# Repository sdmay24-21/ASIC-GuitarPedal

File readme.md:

# Digital ASIC Fabrication
Guitar Pedal IC

Top Level Diagram
## Members
Jonathan Hess\
Haris Khan\
Samuel Heikens\
Yu Wei Tan

## References
Audio samples:

https://shop.karoryfer.com/pages/free-samples

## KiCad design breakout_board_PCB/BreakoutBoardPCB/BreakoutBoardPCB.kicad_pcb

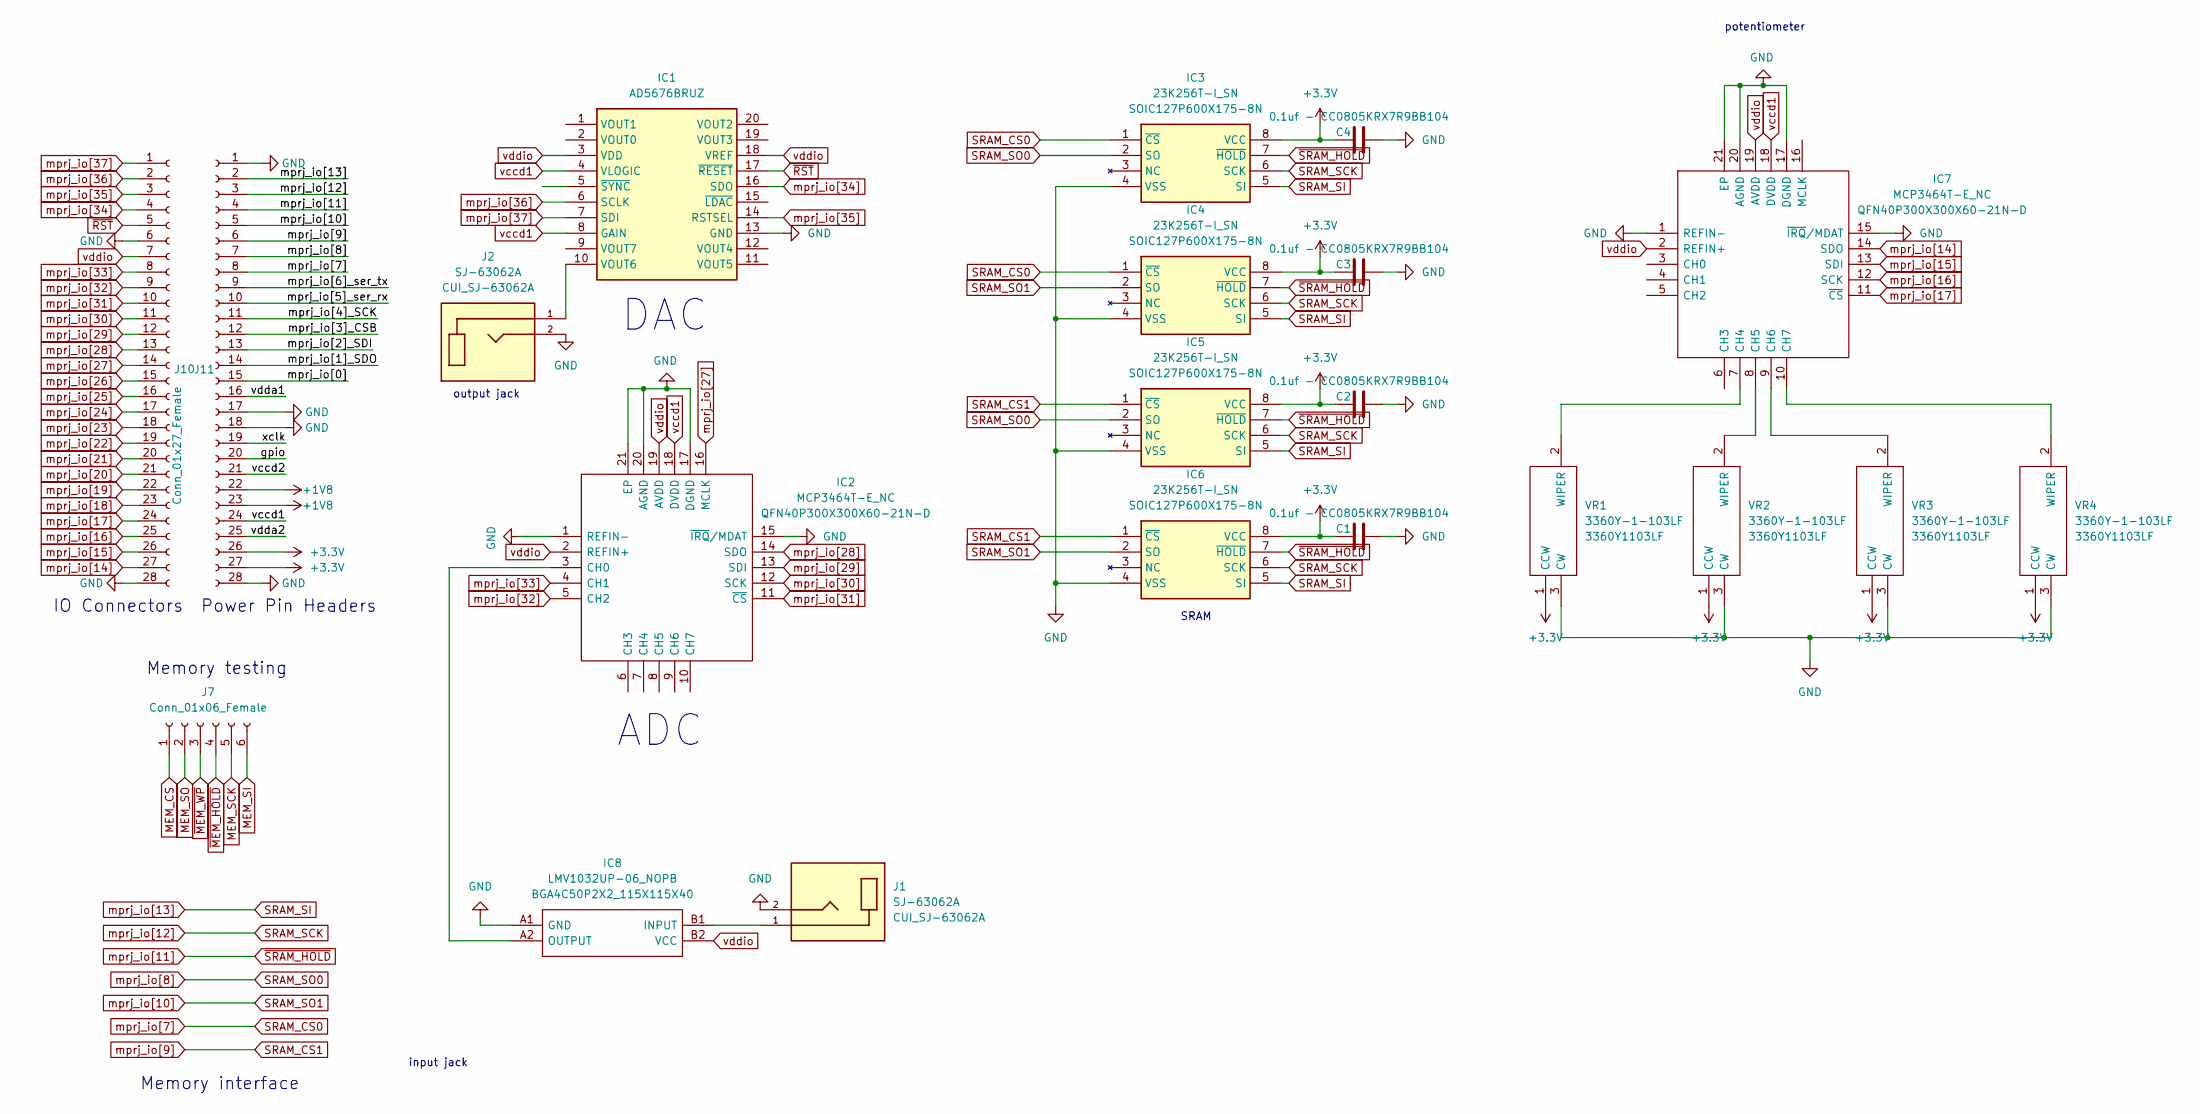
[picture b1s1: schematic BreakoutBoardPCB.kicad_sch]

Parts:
C1, C2, C3, C4: 0.1uf - CC0805KRX7R9BB104; C_0805_2012Metric
IC1: AD5676BRUZ; SOP65P640X120-20N; Mouser Part Number 584-AD5676BRUZ
IC2, IC7: MCP3464T-E_NC; QFN40P300X300X60-21N-D; Mouser Part Number 579-MCP3464T-E/NC
IC3, IC4, IC5, IC6: 23K256T-I_SN; SOIC127P600X175-8N; Mouser Part Number 579-23K256T-I/SN
IC8: LMV1032UP-06_NOPB; BGA4C50P2X2_115X115X40; Mouser Part Number 926-LMV1032UP06NOPB
J1, J2: SJ-63062A; CUI_SJ-63062A
J7: Conn_01x06_Female; PinHeader_1x06_P2.54mm_Vertical
J10: Conn_01x27_Female; PinHeader_1x27_P2.54mm_Vertical
J11: Conn_01x28_Pin; PinHeader_1x28_P2.54mm_Vertical
VR1, VR2, VR3, VR4: 3360Y-1-103LF; 3360Y1103LF; Mouser Part Number 652-3360Y-1-103LF

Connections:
+1V8: J11.22, J11.23
+3.3V: C1.1, C2.1, C3.1, C4.1, IC3.8 (VCC), IC4.8 (VCC), IC5.8 (VCC), IC6.8 (VCC), J11.26, J11.27, VR1.1 (CCW), VR2.1 (CCW), VR3.1 (CCW), VR4.1 (CCW)
/gpio: J11.20
/mprj_io[0]: J11.15
/mprj_io[1]_SDO: J11.14
/mprj_io[2]_SDI: J11.13
/mprj_io[3]_CSB: J11.12
/mprj_io[4]_SCK: J11.11
/mprj_io[5]_ser_rx: J11.10
/mprj_io[6]_ser_tx: J11.9
/vccd2: J11.21
/vdda1: J11.16
/vdda2: J11.25
/xclk: J11.19
GND: C1.2, C2.2, C3.2, C4.2, IC1.13 (GND), IC2.1 (REFIN-), IC2.15 (~IRQ/MDAT), IC2.17 (DGND), IC2.20 (AGND), IC2.21 (EP), IC3.4 (VSS), IC4.4 (VSS), IC5.4 (VSS), IC6.4 (VSS), IC7.1 (REFIN-), IC7.15 (~IRQ/MDAT), IC7.17 (DGND), IC7.20 (AGND), IC7.21 (EP), IC8.A1 (GND), J1.2, J2.2, J10.6, J10.28, J11.1, J11.17, J11.18, J11.28, VR1.3 (CW), VR2.3 (CW), VR3.3 (CW), VR4.3 (CW); also elsewhere on the board
MEM_CS: J7.1
MEM_SCK: J7.5
MEM_SI: J7.6
MEM_SO: J7.2
unnamed: IC1.10 (VOUT6), J2.1
unnamed: IC2.3 (CH0), IC8.A2 (OUTPUT)
unnamed: IC7.7 (CH4), VR1.2 (WIPER)
unnamed: IC7.8 (CH5), VR2.2 (WIPER)
unnamed: IC7.9 (CH6), VR3.2 (WIPER)
unnamed: IC7.10 (CH7), VR4.2 (WIPER)
unnamed: IC8.B1 (INPUT), J1.1
SRAM_CS0: IC3.1 (~CS), IC4.1 (~CS), J11.8
SRAM_CS1: IC5.1 (~CS), IC6.1 (~CS), J11.6
SRAM_SCK: IC3.6 (SCK), IC4.6 (SCK), IC5.6 (SCK), IC6.6 (SCK), J11.3
SRAM_SI: IC3.5 (SI), IC4.5 (SI), IC5.5 (SI), IC6.5 (SI), J11.2
SRAM_SO0: IC3.2 (SO), IC5.2 (SO), J11.7
SRAM_SO1: IC4.2 (SO), IC6.2 (SO), J11.5
mprj_io[11]: IC3.7 (~HOLD), IC4.7 (~HOLD), IC5.7 (~HOLD), IC6.7 (~HOLD), J11.4
mprj_io[14]: IC7.14 (SDO), J10.27
mprj_io[15]: IC7.13 (SDI), J10.26
mprj_io[16]: IC7.12 (SCK), J10.25
mprj_io[17]: IC7.11 (~CS), J10.24
mprj_io[18]: J10.23
mprj_io[19]: J10.22
mprj_io[20]: J10.21
mprj_io[21]: J10.20
mprj_io[22]: J10.19
mprj_io[23]: J10.18
mprj_io[24]: J10.17
mprj_io[25]: J10.16
mprj_io[26]: J10.15
mprj_io[27]: IC2.16 (MCLK), J10.14
mprj_io[28]: IC2.14 (SDO), J10.13
mprj_io[29]: IC2.13 (SDI), J10.12
mprj_io[30]: IC2.12 (SCK), J10.11
mprj_io[31]: IC2.11 (~CS), J10.10
mprj_io[32]: IC2.5 (CH2), J10.9
mprj_io[33]: IC2.4 (CH1), J10.8
mprj_io[34]: IC1.16 (SDO), J10.4
mprj_io[35]: IC1.14 (RSTSEL), J10.3
mprj_io[36]: IC1.6 (SCLK), J10.2
mprj_io[37]: IC1.7 (SDI), J10.1
vccd1: IC1.4 (VLOGIC), IC1.8 (GAIN), IC2.18 (DVDD), IC7.18 (DVDD), J11.24
vddio: IC1.3 (VDD), IC1.18 (VREF), IC2.2 (REFIN+), IC2.19 (AVDD), IC7.2 (REFIN+), IC7.19 (AVDD), IC8.B2 (VCC), J10.7
~MEM_HOLD: J7.4
~MEM_WP: J7.3
~RST: IC1.17 (~RESET), J10.5

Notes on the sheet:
SRAM
potentiometer
Power Pin Headers
ADC
Memory interface
Memory testing
output jack
DAC
IO Connectors
input jack

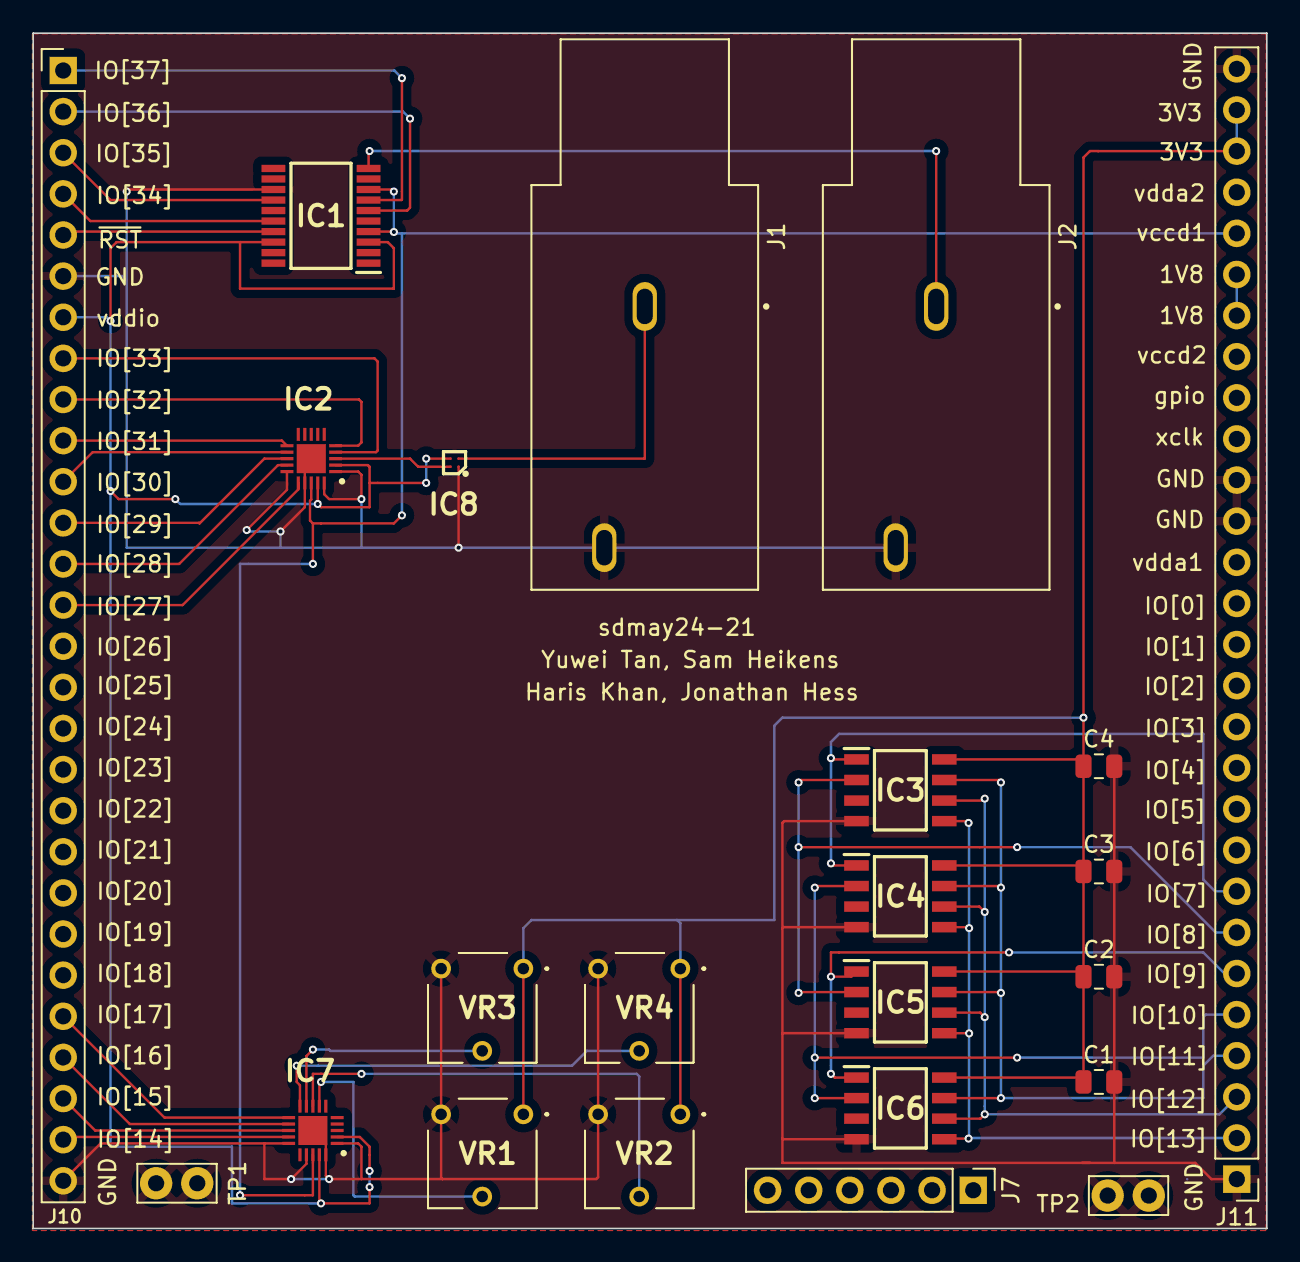
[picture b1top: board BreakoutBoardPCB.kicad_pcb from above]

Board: 2 copper layers, 76.2 x 73.8 mm, 23 parts (0 on the bottom side), 35 nets.

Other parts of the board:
TP1, TP2: TestPoint; TestPoint_Bridge_Pitch2.54mm_Drill1.0mm

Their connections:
GND: TP1.1, TP2.1; also elsewhere on the board

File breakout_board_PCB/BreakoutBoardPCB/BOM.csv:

"Reference","Value","Datasheet","Footprint","Qty","DNP"
"C1,C2,C3,C4","0.1uf - CC0805KRX7R9BB104","~","Capacitor_SMD:C_0805_2012Metric","4",""
"IC1","AD5676BRUZ","https://www.analog.com/AD5676/datasheet","SeniorDesign:SOP65P640X120-20N","1",""
"IC2,IC7","MCP3464T-E_NC","http://www.microchip.com/mymicrochip/filehandler.aspx?ddocna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","QFN40P300X300X60-21N-D","2",""
"IC3,IC4,IC5,IC6","23K256T-I_SN","http://www.microchip.com/mymicrochip/filehandler.aspx?ddocna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","SOIC127P600X175-8N","4",""
"IC8","LMV1032UP-06_NOPB","http://www.ti.com/lit/gpn/lmv1032","BGA4C50P2X2_115X115X40","1",""
"J1,J2","SJ-63062A","","CUI_SJ-63062A","2",""
"J7","Conn_01x06_Female","~","Connector_PinHeader_2.54mm:PinHeader_1x06_P2.54mm_Vertical","1",""
"J10","Conn_01x27_Female","~","Connector_PinHeader_2.54mm:PinHeader_1x27_P2.54mm_Vertical","1",""
"J11","Conn_01x28_Pin","~","Connector_PinHeader_2.54mm:PinHeader_1x28_P2.54mm_Vertical","1",""
"VR1,VR2,VR3,VR4","3360Y-1-103LF","http://www.bourns.com/docs/Product-Datasheets/3360.pdf","3360Y1103LF","4",""

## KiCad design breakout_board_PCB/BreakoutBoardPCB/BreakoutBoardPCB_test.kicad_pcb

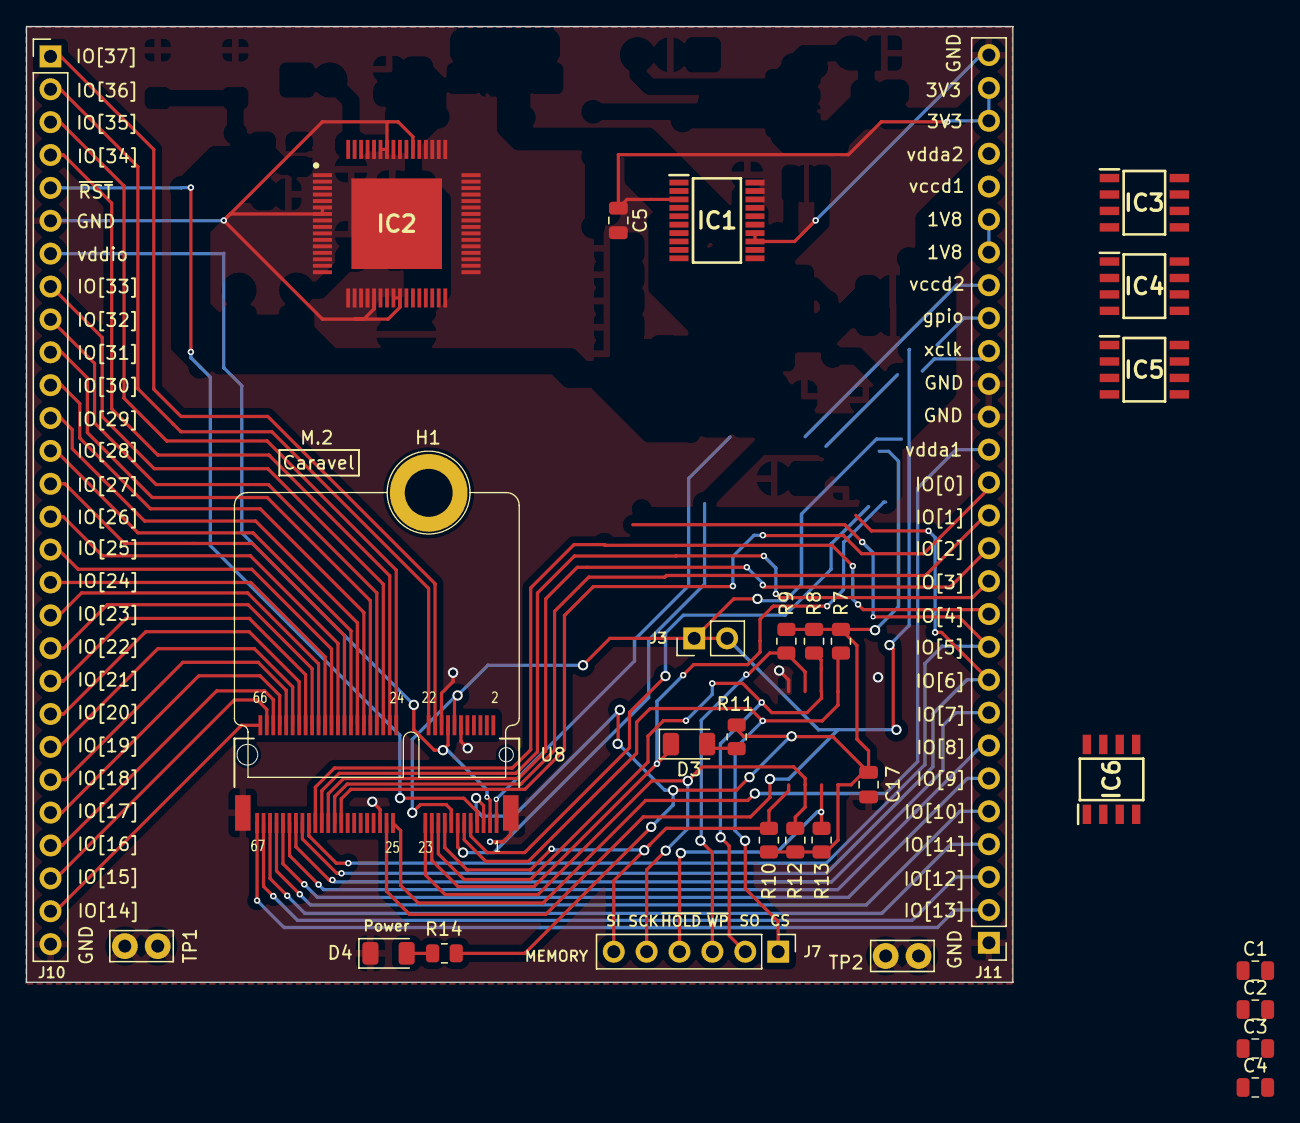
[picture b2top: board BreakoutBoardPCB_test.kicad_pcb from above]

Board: 2 copper layers, 76.2 x 73.8 mm, 30 parts (0 on the bottom side), 56 nets.

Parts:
C1, C2, C3, C4, C5, C17: 0.1uf - CC0805KRX7R9BB104; C_0805_2012Metric
D3, D4: LED - 17-215SURC/S530-A2/TR8; LED_1206_3216Metric
H1: MICROMOD-Standoff; MicroMod-Standoff
IC1: AD5676BRUZ; SOP65P640X120-20N
IC2: ADS1178IPAPT; QFP50P1200X1200X120-65N
IC3, IC4, IC5, IC6: 23K256T-I_SN; SOIC127P600X175-8N
J3: Conn_01x02_Male; PinHeader_1x02_P2.54mm_Vertical
J7: Conn_01x06_Female; PinHeader_1x06_P2.54mm_Vertical
J10: Conn_01x27_Female; PinHeader_1x28_P2.54mm_Vertical
J11: Conn_01x20_Female; PinHeader_1x28_P2.54mm_Vertical
R7, R8, R9, R10, R12, R13: 10k - RC0805FR-0710KL; R_0805_2012Metric
R11, R14: 82 - 0805W8F820JT5E; R_0805_2012Metric
TP1, TP2: TestPoint; TestPoint_Bridge_Pitch2.54mm_Drill1.0mm
U8: caravel-M.2-card; M.2-CONNECTOR-E

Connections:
+3.3V: C1.1, C2.1, C3.1, C4.1, IC3.8 (VCC), IC4.8 (VCC), IC5.8 (VCC), IC6.8 (VCC)
Caravel_CSB: J7.1, R7.1, U8.11 (Caravel_CSB)
Caravel_D0: J7.6, R10.1, U8.17 (Caravel_D0)
Caravel_D1: J7.2, R8.1, U8.19 (Caravel_D1)
Caravel_SCK: J7.5, R12.1, U8.23 (Caravel_SCK)
GND: C1.2, C2.2, C3.2, C4.2, C5.2, C17.2, D4.1 (K), IC1.13 (GND), IC1.14 (RSTSEL), IC2.6 (AGND_1), IC2.7 (DGND_1), IC2.21 (DGND_2), IC2.24 (DGND_3), IC2.25 (DGND_4), IC2.54 (AGND_3), IC2.58 (AGND_4), IC2.59 (AGND_5), IC3.4 (VSS), IC4.4 (VSS), IC5.4 (VSS), IC6.4 (VSS), J10.6, J10.28, J11.1, J11.17, J11.18, J11.28, TP1.1, TP2.1, U8.12 (GND), U8.18 (GND), U8.37 (GND), U8.A1 (GND), U8.A2 (GND)
unnamed: D3.2 (A), R11.2
unnamed: D4.2 (A), R14.2
USB_CS1: J11.12, U8.55 (mprj_io[3]_CSB)
USB_SCK_TXD: J11.11, U8.57 (mprj_io[4]_SCK)
USB_SI: J11.14, U8.51 (mprj_io[1]_SDO)
USB_SO_RXD: J11.13, U8.53 (mprj_io[2]_SDI)
gpio: D3.1 (K), J11.20, U8.21 (gpio)
mprj_io[0]: J11.15, U8.49 (mprj_io[0])
mprj_io[5]_ser_rx: J11.10, U8.59 (mprj_io[5]_ser_rx)
mprj_io[6]_ser_tx: J11.9, U8.61 (mprj_io[6]_ser_tx)
mprj_io[7]: J11.8, U8.63 (mprj_io[7])
mprj_io[8]: J11.7, U8.65 (mprj_io[8])
mprj_io[9]: J11.6, U8.67 (mprj_io[9])
mprj_io[10]: J11.5, U8.69 (mprj_io[10])
mprj_io[11]: J11.4, U8.71 (mprj_io[11])
mprj_io[12]: J11.3, U8.73 (mprj_io[12])
mprj_io[13]: J11.2, U8.75 (mprj_io[13])
mprj_io[14]: J10.27, U8.74 (mprj_io[14])
mprj_io[15]: J10.26, U8.72 (mprj_io[15])
mprj_io[16]: J10.25, U8.70 (mprj_io[16])
mprj_io[17]: J10.24, U8.68 (mprj_io[17])
mprj_io[18]: J10.23, U8.66 (mprj_io[18])
mprj_io[19]: J10.22, U8.64 (mprj_io[19])
mprj_io[20]: J10.21, U8.62 (mprj_io[20])
mprj_io[21]: J10.20, U8.60 (mprj_io[21])
mprj_io[22]: J10.19, U8.58 (mprj_io[22])
mprj_io[23]: J10.18, U8.56 (mprj_io[23])
mprj_io[24]: J10.17, U8.54 (mprj_io[24])
mprj_io[25]: J10.16, U8.52 (mprj_io[25])
mprj_io[26]: J10.15, U8.50 (mprj_io[26])
mprj_io[27]: J10.14, U8.48 (mprj_io[27])
mprj_io[28]: J10.13, U8.46 (mprj_io[28])
mprj_io[29]: J10.12, U8.44 (mprj_io[29])
mprj_io[30]: J10.11, U8.42 (mprj_io[30])
mprj_io[31]: J10.10, U8.40 (mprj_io[31])
mprj_io[32]: J10.9, U8.38 (mprj_io[32])
mprj_io[33]: J10.8, U8.36 (mprj_io[33])
mprj_io[34]: J10.4, U8.34 (mprj_io[34])
mprj_io[35]: J10.3, U8.32 (mprj_io[35])
mprj_io[36]: J10.2, U8.22 (mprj_io[36])
mprj_io[37]: J10.1, U8.20 (mprj_io[37])
vccd: J3.1, J3.2, J11.22, J11.23, J11.24, U8.14 (vccd), U8.15 (vcdd), U8.35 (vccd1)
vccd2: J11.21, U8.1 (vccd2)
vdda: C5.1, C17.1, IC1.3 (VDD), J10.7, J11.26, J11.27, R7.2, R8.2, R9.2, R10.2, R11.1, R12.2, R13.2, R14.1, U8.3 (vddio), U8.5 (vdda), U8.16 (vddio)
vdda1: J11.16, U8.33 (vdda1)
vdda2: J11.25, U8.13 (vdda2)
xclk: J11.19, U8.9 (xclk)
~MEM_HOLD: J7.4, R13.1
~MEM_WP: J7.3, R9.1
~RST: J10.5, U8.7 (~RST)

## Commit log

2023-10-25 update to gitlab
2023-10-25 Remove termp readme
2023-10-25 Update readme and docs structure
2023-10-26 Added Memory Controller Diagram
2023-10-26 added memory controller stub and updated diagram
2023-10-26 Added compression and updated memory controller
2023-10-26 Fixed reverb spelling mistake
2023-10-28 Pedal top level and wrapper start
2023-10-28 Git ignore and design info update
2023-11-01 Started creating top level design
2023-11-01 Top Level Diagram Update
2023-11-01 Resize spi controller in diagram
2023-11-01 dpi change
2023-11-07 Impulse Audio Testing
2023-11-13 Tested Verilator and added top level tbs
2023-11-13 Updated userproject runner (will fail)
2023-11-14 Retry docker
2023-11-14 Removed usese
2023-11-14 Retry Docker with cd after docker
2023-11-14 Remove -ti
2023-11-14 Not home directory
2023-11-14 Fix CD
2023-11-15 Fix local version
2023-11-15 Trying new docker task
2023-11-15 Not TTY
2023-11-15 Docker image run
2023-11-16 Start top level sim CPP code
2023-11-16 add act
2023-11-16 add main to python
2023-11-28 sim coding start
2023-11-30 PCB Level Diagram
2024-01-24 Added Compression Module from Sam
2024-01-24 Added Compression via Sam
2024-01-31 audiopy change
2024-02-16 memory controller start
2024-02-16 Added Compression Test to CI
2024-02-16 Added Compression_Test Wrapper and changed make command in Compression_Test
2024-03-01 Memory controller work
2024-03-07 Verilator for Memory controller start
2024-03-27 memory controller test data python code
2024-03-27 pedal top updates
2024-03-27 Added PCB start
2024-03-28 test
2024-03-30 Update config.json
    Line 6 was changed. pedal_top.v matches the file in the verilog folder. Not, pedal_top_level.v.
2024-03-30 Errors in hardening process
    %Warning-EOFNEWLINE: /home/sheikens/ASIC-GuitarPedal/openlane/pedal_ASIC/../../verilog/rtl/pedal_top.v:184:10: Missing newline at end of file (POSIX 3.206).
    : ... Suggest add newline.
    184 | endmodule
    | ^
    %Error: /home/sheikens/ASIC-GuitarPedal/openlane/pedal_ASIC/../../verilog/rtl/pedal_top.v:41:5: syntax error, unexpected wire, expecting ',' or ';'
    41 | wire cs = io_out[2];
2024-03-30 New line at end
    %Warning-EOFNEWLINE: /home/sheikens/ASIC-GuitarPedal/openlane/pedal_ASIC/../../verilog/rtl/defines.v:66:28: Missing newline at end of file (POSIX 3.206).
    : ... Suggest add newline.
    66 | `endif // __GLOBAL_DEFINE_H
    | ^
    ... For warning description see https://verilator.org/warn/EOFNEWLINE?v=5.009
    ... Use "/* verilator lint_off EOFNEWLINE */" and lint_on around source to disable this message.
2024-03-30 Update Makefile: https://git-pages.ece.iastate.edu/isu-chip-fab/documentation/#/caravel/introduction
    Instruction from sddec23-06
    The root level Makefile in the caravel repo will need to be updated, since there is currently an issue with building cocotb, which is not essential for running the tools. To do this, do the following:
    In the root repository, open the Makefile with vi Makefile
    In the text editor, enter /setup
    Navigate to the line .PHONY: setup
    While searching the string, press n to navigate to next string
2024-03-30 Update pedal_top.v
    %Error: /home/sheikens/ASIC-GuitarPedal/openlane/pedal_ASIC/../../verilog/rtl/pedal_top.v:79:21: syntax error, unexpected '[', expecting IDENTIFIER or do or final or randomize
    79 | wire memory_we, [32:0]mem_address, mem_output[15:0];
    | ^
    %Error: Exiting due to 1 error(s)
2024-03-30 There was an extra comma.
    %Error: /home/sheikens/ASIC-GuitarPedal/openlane/pedal_ASIC/../../verilog/rtl/pedal_top.v:169:5: Mixing positional and .*/named instantiation connection (IEEE 1800-2017 23.3.2)
    169 | );
2024-03-30 Update pedal_top.v
    %Error: Specified --top-module 'pedal_ASIC' was not found in design.
2024-03-30 Update includes.gl+sdf.caravel_user_project
    %Error: /home/sheikens/ASIC-GuitarPedal/openlane/pedal_ASIC/../../verilog/rtl/pedal_top.v:107:5: Cannot find file containing module: 'sram_1rw1r_32_256_8_sky130'
    107 | sram_1rw1r_32_256_8_sky130 sram_memmory(
2024-03-30 Update includes.gl.caravel_user_project
    %Error: /home/sheikens/ASIC-GuitarPedal/openlane/pedal_ASIC/../../verilog/rtl/pedal_top.v:107:5: Cannot find file containing module: 'sram_1rw1r_32_256_8_sky130'
    107 | sram_1rw1r_32_256_8_sky130 sram_memmory(
2024-03-30 Update includes.rtl.caravel_user_project
    %Error: /home/sheikens/ASIC-GuitarPedal/openlane/pedal_ASIC/../../verilog/rtl/pedal_top.v:107:5: Cannot find file containing module: 'sram_1rw1r_32_256_8_sky130'
    107 | sram_1rw1r_32_256_8_sky130 sram_memmory(
2024-03-30 Trying to fix SRAM
2024-04-01 update again
2024-04-02 Update config.json
    Include verilog files for hardening to work.
2024-04-02 Update config.json
    missing comma
2024-04-02 .wmask0(), Is in instantiation but not in the sram file itself.
2024-04-02 Verilog Includes
2024-04-02 modify file paths for includes
2024-04-02 Issues with Hardening
2024-04-02 Hardening
2024-04-02 Hardening Issues
2024-04-02 Verilog Fixes
2024-04-02 Compresssion Fix
2024-04-02 Mux and SPI added
2024-04-03 Memory Fixes
2024-04-03 Compression Fixes
2024-04-03 mux fix
2024-04-03 Mux Fixes
2024-04-03 SPI includes and fixes
2024-04-03 SPI fixes
2024-04-03 SPI Fix
2024-04-05 update 4/5
2024-04-11 Memory Controller Python
2024-04-12 last update
2024-04-16 SPI removed
2024-04-16 mem_output specifications in memorycontroller
2024-04-16 completely fixing all our problems
2024-04-16 adder
2024-04-16 controller commented out
2024-04-16 add adder
2024-04-16 adder instantiation fixed
2024-04-16 modifying SRAM timing
2024-04-16 removing delay from SRAM
2024-04-16 DELAY changes
2024-04-16 timing fixes
2024-04-16 error from errors, changed to issues
2024-04-16 same thing
2024-04-16 %Error-PROCASSWIRE: /home/sheikens/ASIC-GuitarPedal/openlane/pedal_ASIC/../../verilog/rtl/memory/memorycontroller.v:48:13: Procedural assignment to wire, perhaps intended var (IEEE 1800-2017 6.5): 'm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
2024-04-17 remove second pedal_top.c
2024-04-17 trying to get make setup working again
2024-04-19 Python test data for memory controller
2024-04-19 Mem control verilator
2024-04-19 update to MPW
2024-04-19 change MPW
2024-04-19 Verilator got mem controller to compile
2024-04-20 copy and paste updated Makefile from caravel_user_project to get make setup to work
2024-04-22 Verilator testing begins
2024-04-22 spi module
2024-04-22 Memory Controller Debugging
2024-04-23 Memory controller testing code complete, now just debugging overflow
2024-04-24 Memory controller main function finished (need override for loading impulses)
2024-04-24 Memory Controller still has errors
2024-04-28 Updated Top Level Diagram PNG
2024-04-28 Rename Top Level Diagram.png to TopLevelDiagram.png
2024-05-19 Start on top level changes
